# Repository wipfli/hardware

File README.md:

# hardware
Hardware design files for the ballometer

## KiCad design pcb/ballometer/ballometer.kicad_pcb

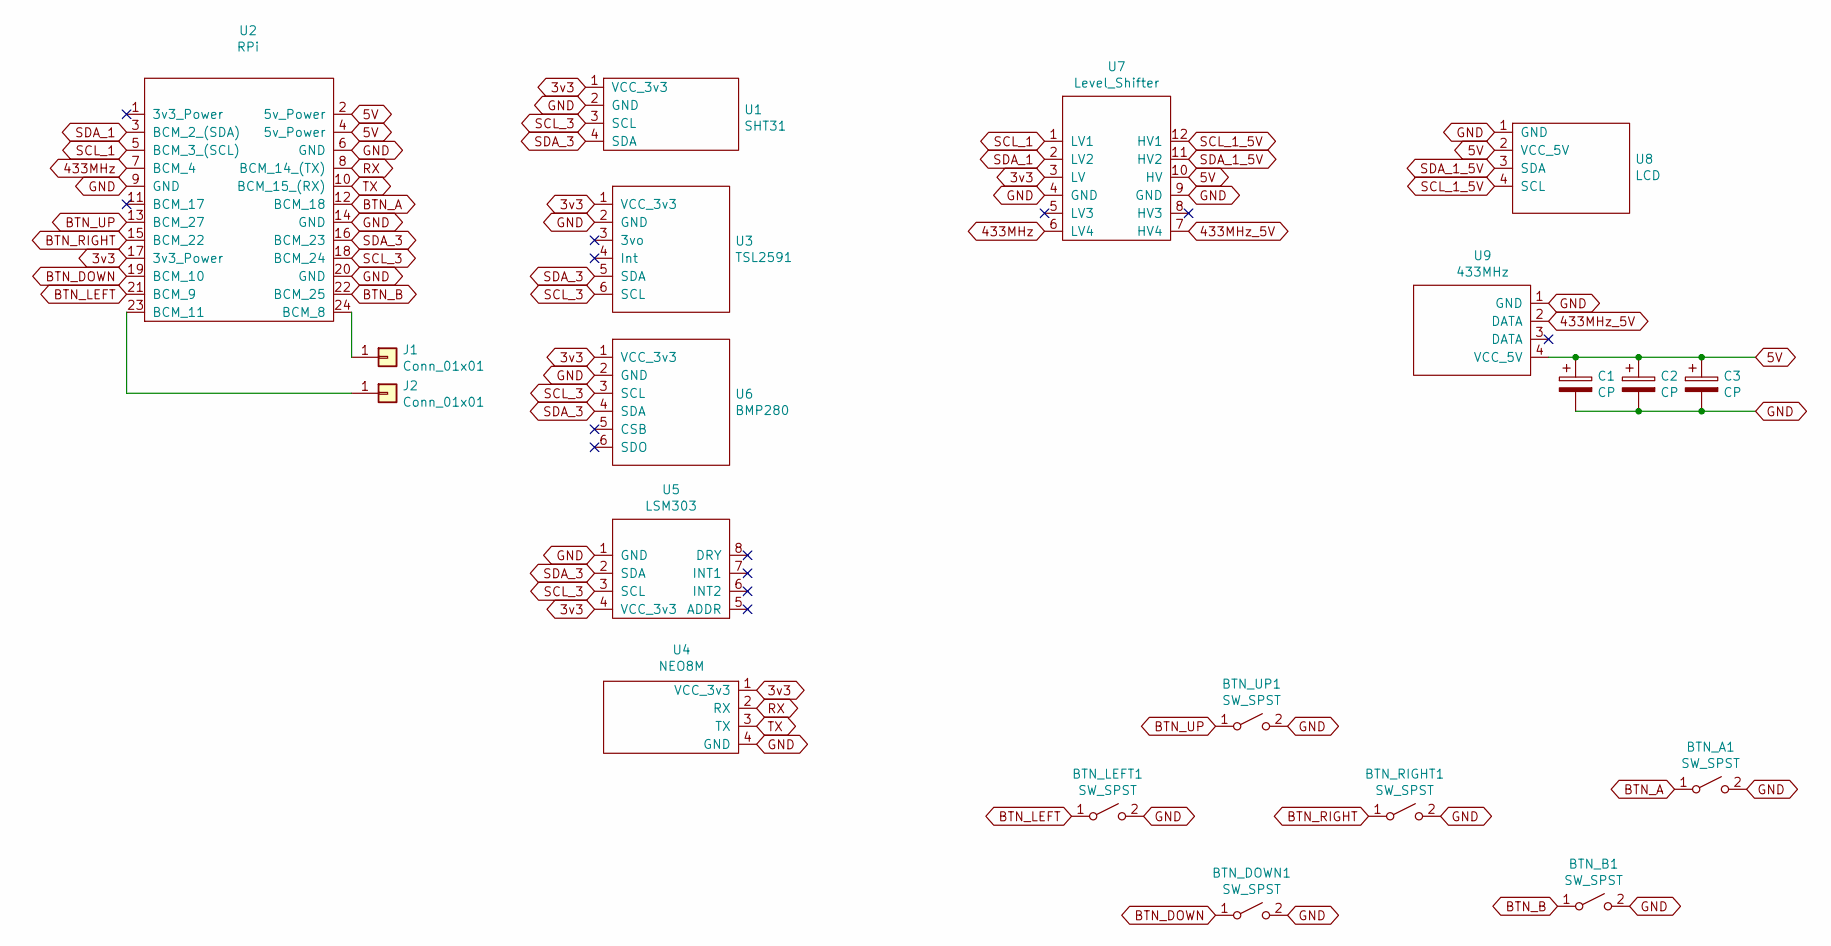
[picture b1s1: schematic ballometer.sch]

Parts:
BTN_A1: SW_SPST; SW_PUSH_6mm_H4.3mm
BTN_B1: SW_SPST; SW_PUSH_6mm_H4.3mm
BTN_DOWN1: SW_SPST; SW_PUSH_6mm_H4.3mm
BTN_LEFT1: SW_SPST; SW_PUSH_6mm_H4.3mm
BTN_RIGHT1: SW_SPST; SW_PUSH_6mm_H4.3mm
BTN_UP1: SW_SPST; SW_PUSH_6mm_H4.3mm
C1: CP; CP_Radial_D10.0mm_P5.00mm
C2, C3: CP; PinHeader_1x02_P2.54mm_Vertical
J1, J2: Conn_01x01; PinHeader_1x01_P2.54mm_Vertical
U1: SHT31
U2: RPi; PinHeader_2x12_P2.54mm_Vertical
U3: TSL2591; TLS2591
U4: NEO8M
U5: LSM303
U6: BMP280
U7: Level_Shifter
U8: LCD
U9: 433MHz

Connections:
3v3: U1.1 (VCC_3v3), U2.17 (3v3_Power), U3.1 (VCC_3v3), U4.1 (VCC_3v3), U5.4 (VCC_3v3), U6.1 (VCC_3v3), U7.3 (LV)
5V: C1.1, C2.1, C3.1, U2.2 (5v_Power), U2.4 (5v_Power), U7.10 (HV), U8.2 (VCC_5V), U9.4 (VCC_5V)
433MHz: U2.7 (BCM_4), U7.6 (LV4)
433MHz_5V: U7.7 (HV4), U9.2 (DATA)
BTN_A: BTN_A1.1 (A), U2.12 (BCM_18)
BTN_B: BTN_B1.1 (A), U2.22 (BCM_25)
BTN_DOWN: BTN_DOWN1.1 (A), U2.19 (BCM_10)
BTN_LEFT: BTN_LEFT1.1 (A), U2.21 (BCM_9)
BTN_RIGHT: BTN_RIGHT1.1 (A), U2.15 (BCM_22)
BTN_UP: BTN_UP1.1 (A), U2.13 (BCM_27)
GND: BTN_A1.2 (B), BTN_B1.2 (B), BTN_DOWN1.2 (B), BTN_LEFT1.2 (B), BTN_RIGHT1.2 (B), BTN_UP1.2 (B), C1.2, C2.2, C3.2, U1.2 (GND), U2.6 (GND), U2.9 (GND), U2.14 (GND), U2.20 (GND), U3.2 (GND), U4.4 (GND), U5.1 (GND), U6.2 (GND), U7.4 (GND), U7.9 (GND), U8.1 (GND), U9.1 (GND)
unnamed: J1.1, U2.24 (BCM_8)
unnamed: J2.1, U2.23 (BCM_11)
RX: U2.8 (BCM_14_(TX)), U4.2 (RX)
SCL_1: U2.5 (BCM_3_(SCL)), U7.1 (LV1)
SCL_1_5V: U7.12 (HV1), U8.4 (SCL)
SCL_3: U1.3 (SCL), U2.18 (BCM_24), U3.6 (SCL), U5.3 (SCL), U6.3 (SCL)
SDA_1: U2.3 (BCM_2_(SDA)), U7.2 (LV2)
SDA_1_5V: U7.11 (HV2), U8.3 (SDA)
SDA_3: U1.4 (SDA), U2.16 (BCM_23), U3.5 (SDA), U5.2 (SDA), U6.4 (SDA)
TX: U2.10 (BCM_15_(RX)), U4.3 (TX)

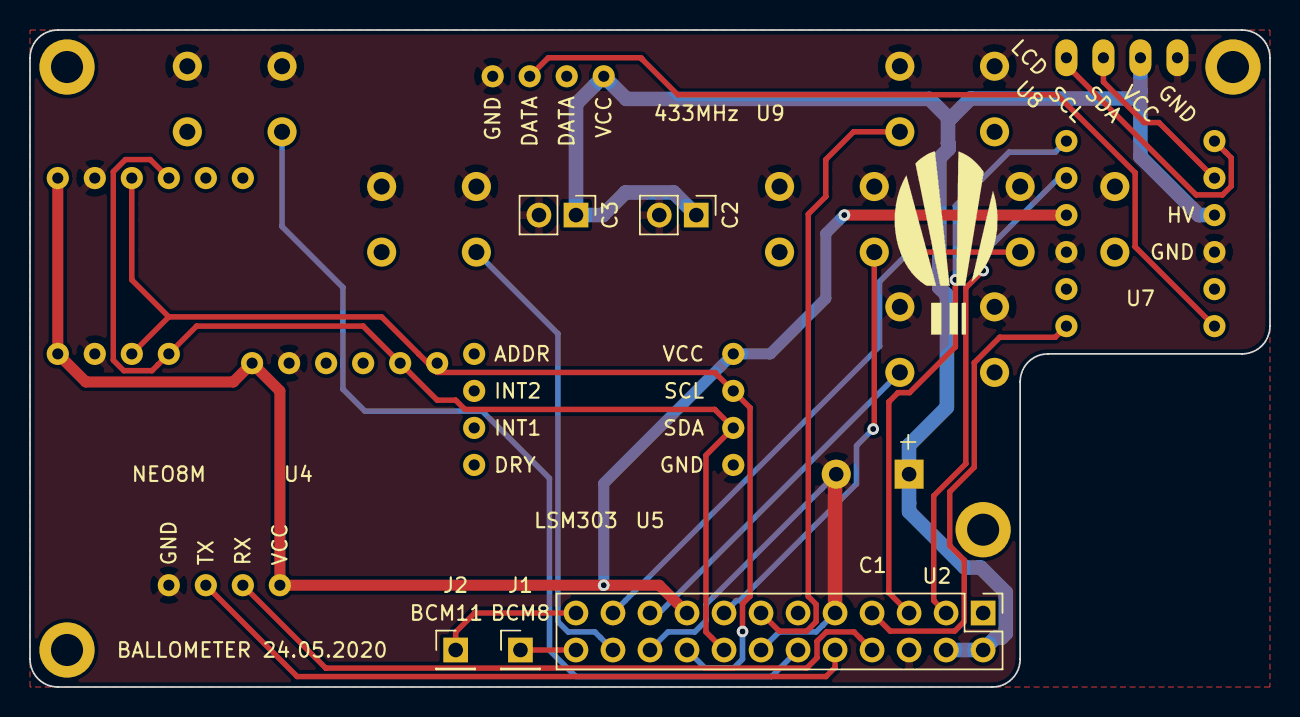
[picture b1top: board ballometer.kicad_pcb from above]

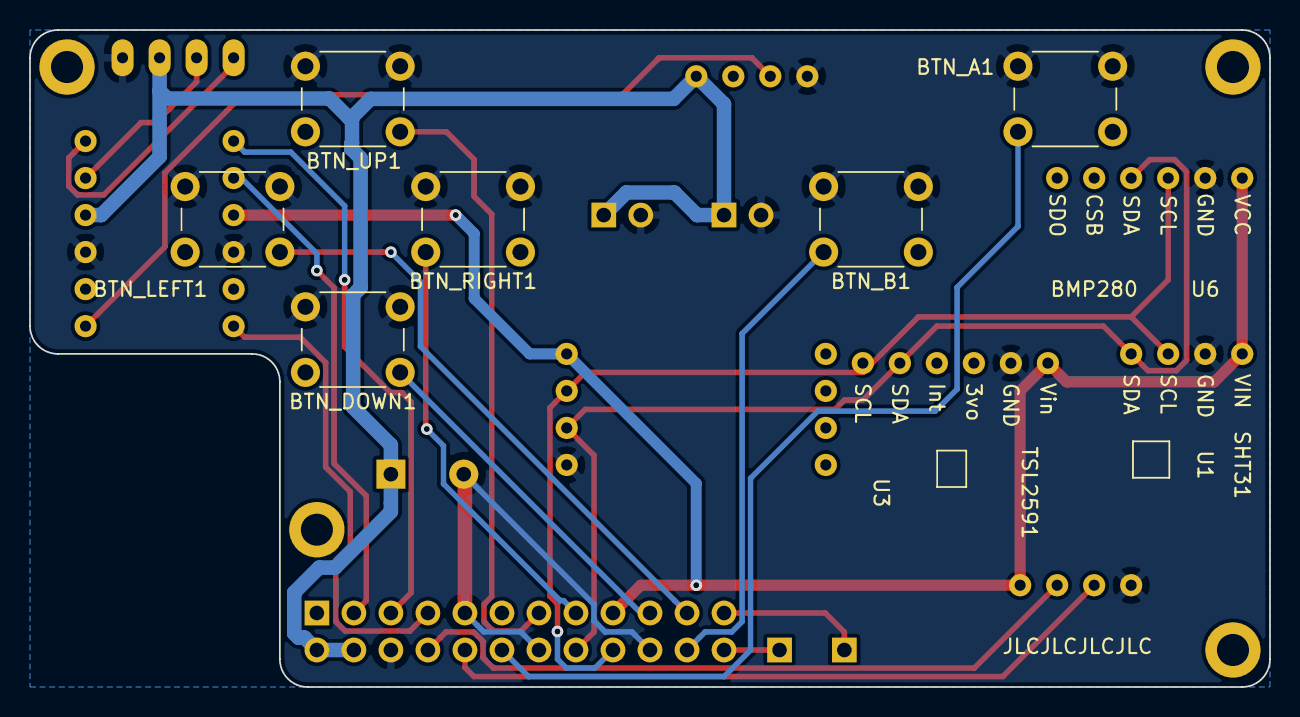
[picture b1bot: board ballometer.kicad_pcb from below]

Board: 2 copper layers, 85.1 x 45.1 mm, 20 parts (9 on the bottom side), 21 nets.

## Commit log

2020-09-22 PCB files of the first batch
2020-09-23 Add box folder
2020-09-24 Add *.svg to .gitignore
2020-09-24 Add box-rev-2 changes to README.md
2020-09-29 Box revision 3
2020-10-14 Increase wall thicknesss to 3 mm
2020-10-20 Add components.ipynb
2020-10-20 Add .gitignore
2021-06-18 Add components.csv
2021-06-18 Fill csv with aliexpress / digitec components
2021-06-18 Remove components jupyter notebook
2021-06-20 Add ribbon cable
